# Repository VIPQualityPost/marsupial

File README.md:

# MARSUPIAL USB-PD + data hub
Marsupial (Motor And Regular Stuff USB PD Injector And Link) is a two port USB FS/HS hub which also is capable of injecting up to 60W per port (or 100W per port if I can implement USB PD EPR messages). The intended use for this is to be able to power and control motors over a single wire to both the motor and the PC, although it is fully USB PD compliant so you would be able to plug any other type of device into it. At the heart of the design is a programmable buck converter circuit which has a few predefined levels (5V, 9V, 12V, 15V, 20V, all at 3A, or 5A with EPR). In the future I would like to be able to implement Programmable Power Supply (PPS) functionality but at the moment this is out of scope of the project. It requires a large external 24V 120W power supply in order to power each port, and also features a daisy-chain connector on the back so that if you have multiple boards and a more powerful supply, you do not need to wire them all separately. The USB lines are brought out separately on an FFC connector so that the hub may be omitted and the signals manually handled off-board if desired.

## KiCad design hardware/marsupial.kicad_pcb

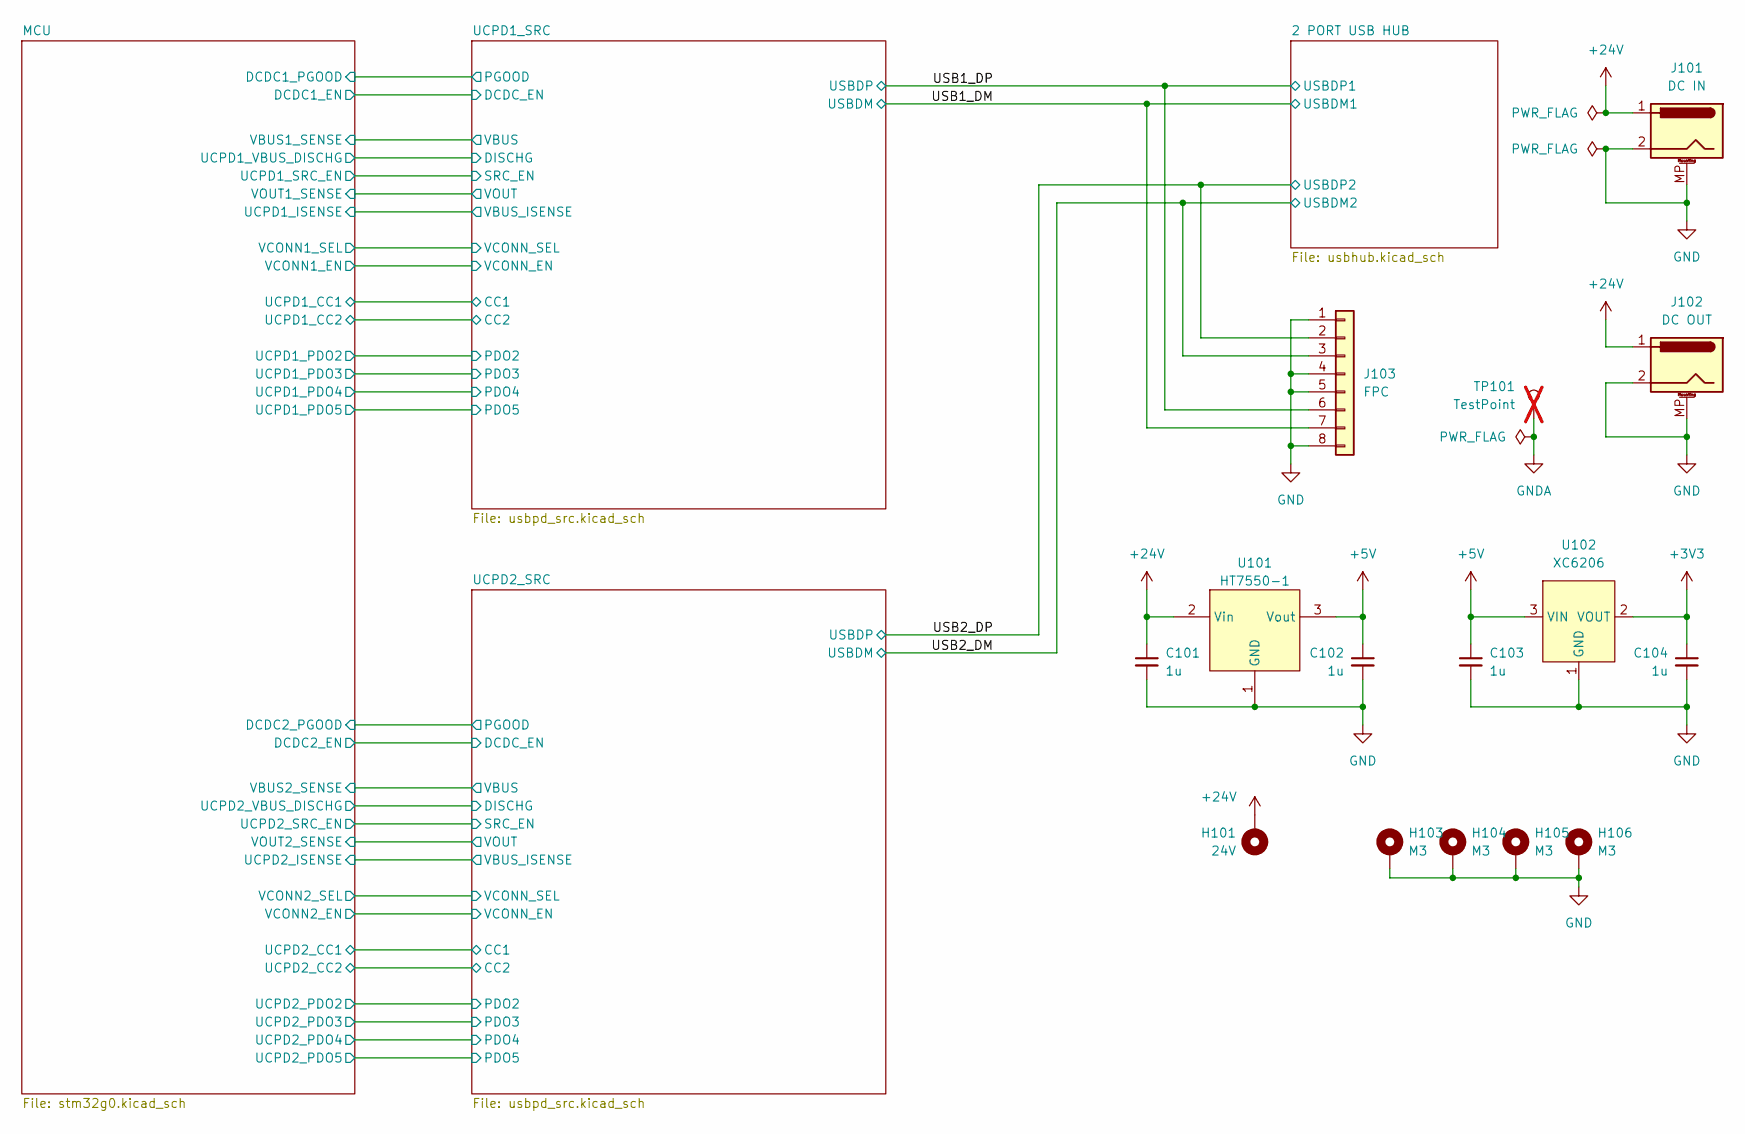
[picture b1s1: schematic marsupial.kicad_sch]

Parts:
C101, C102, C103, C104: 1u; C_0603_1608Metric; LCSC ID C15849
H101: 24V; MountingHole_3.2mm_M3_DIN965_Pad
H103, H104, H105, H106: M3; MountingHole_3.2mm_M3_DIN965_Pad
J101: DC IN; CONN-TH_XT30PW-M; LCSC ID C431092
J102: DC OUT; CONN-TH_XT30PW-M; LCSC ID C431092
J103: FPC; FPC-SMD_8P-P0.50_FPC-05F-8PH20; LCSC ID C2856797
TP101: TestPoint; not fitted
U101: HT7550-1; SOT-89-3; LCSC ID C16106
U102: XC6206; SOT-23; LCSC ID C5446

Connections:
+3V3: C104.1, U102.2 (VOUT); also elsewhere on the board
+5V: C102.1, C103.1, U101.3 (Vout), U102.3 (VIN); also elsewhere on the board
+24V: C101.1, H101.1, J101.1, J102.1, U101.2 (Vin); also elsewhere on the board
/USB1_DM: J103.7; also elsewhere on the board
/USB1_DP: J103.6; also elsewhere on the board
/USB2_DM: J103.3; also elsewhere on the board
/USB2_DP: J103.2; also elsewhere on the board
GND: C101.2, C102.2, C103.2, C104.2, H103.1, H104.1, H105.1, H106.1, J101.2, J101.MP (MountPin), J102.2, J102.MP (MountPin), J103.1, J103.4, J103.5, J103.8, U101.1 (GND), U102.1 (GND); also elsewhere on the board

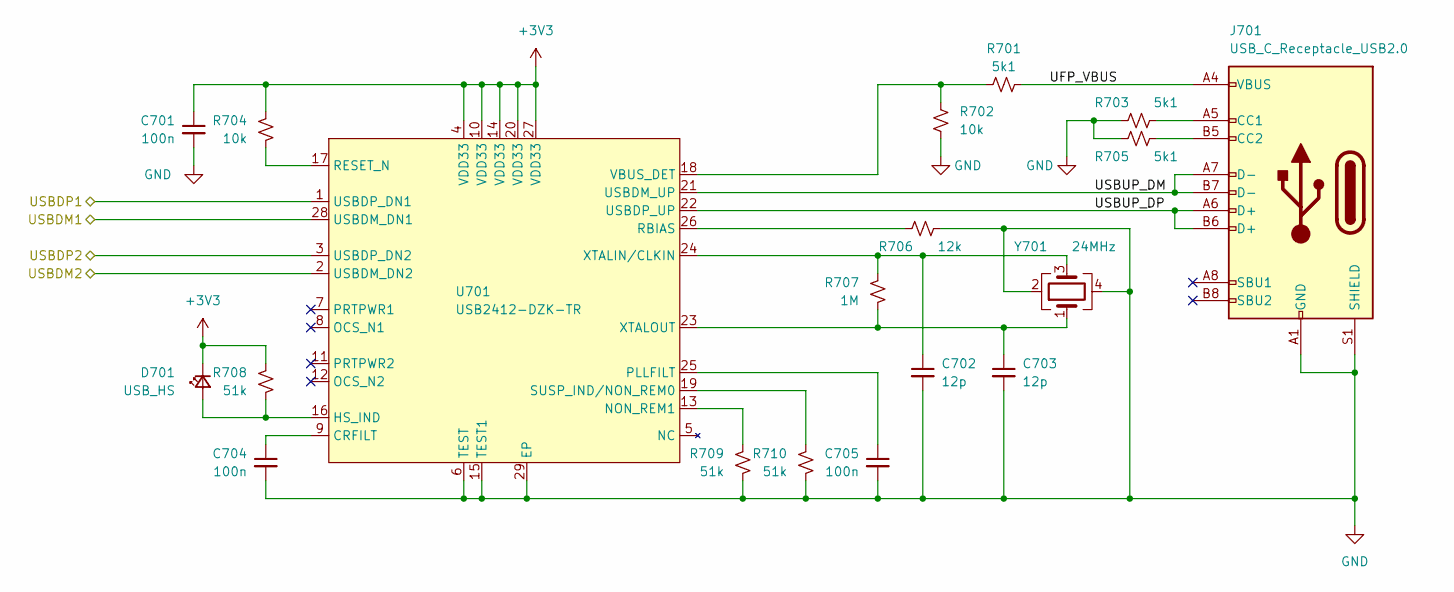
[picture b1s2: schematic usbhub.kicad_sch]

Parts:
C701: 100n; C_0402_1005Metric; LCSC ID C307331
C702, C703: 12p; C_0402_1005Metric; LCSC ID C1547
C704, C705: 100n; C_0603_1608Metric; LCSC ID C14663
D701: USB_HS; D_0603_1608Metric; LCSC ID C2290
J701: USB_C_Receptacle_USB2.0; HRO-TYPE-C-31-M-12; LCSC ID C165948
R701, R703, R705: 5k1; R_0402_1005Metric; LCSC ID C25905
R702, R704: 10k; R_0402_1005Metric; LCSC ID C25744
R706: 12k; R_0402_1005Metric; LCSC ID C25752
R707: 1M; R_0402_1005Metric; LCSC ID C26083
R708, R709, R710: 51k; R_0402_1005Metric; LCSC ID C25794
U701: USB2412-DZK-TR; QFN-28_L5.0-W5.0-P0.50-BL-EP3.3; LCSC ID C622609
Y701: 24MHz; Crystal_SMD_3225-4Pin_3.2x2.5mm; LCSC ID C70590

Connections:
+3V3: C701.1, D701.1 (K), R704.1, R708.1, U701.4 (VDD33), U701.10 (VDD33), U701.14 (VDD33), U701.20 (VDD33), U701.27 (VDD33); also elsewhere on the board
/2 PORT USB HUB/UFP_VBUS: J701.A4 (VBUS), J701.A9 (VBUS), J701.B4 (VBUS), J701.B9 (VBUS), R701.2
/2 PORT USB HUB/USBUP_DM: J701.A7 (D-), J701.B7 (D-), U701.21 (USBDM_UP)
/2 PORT USB HUB/USBUP_DP: J701.A6 (D+), J701.B6 (D+), U701.22 (USBDP_UP)
/USB1_DM: U701.28 (USBDM_DN1); also elsewhere on the board
/USB1_DP: U701.1 (USBDP_DN1); also elsewhere on the board
/USB2_DM: U701.2 (USBDM_DN2); also elsewhere on the board
/USB2_DP: U701.3 (USBDP_DN2); also elsewhere on the board
GND: C701.2, C702.2, C703.2, C704.2, C705.2, J701.A1 (GND), J701.A12 (GND), J701.B1 (GND), J701.B12 (GND), J701.S1 (SHIELD), R702.2, R703.1, R705.2, R706.1, R709.2, R710.2, U701.6 (TEST), U701.15 (TEST1), U701.29 (EP), Y701.2, Y701.4; also elsewhere on the board
unnamed: D701.2 (A), R708.2, U701.16 (HS_IND)
unnamed: J701.A5 (CC1), R703.2
unnamed: J701.B5 (CC2), R705.1
unnamed: C704.1, U701.9 (CRFILT)
unnamed: R709.1, U701.13 (NON_REM1)
unnamed: C705.1, U701.25 (PLLFILT)
unnamed: R706.2, U701.26 (RBIAS)
unnamed: R704.2, U701.17 (RESET_N)
unnamed: R710.1, U701.19 (SUSP_IND/NON_REM0)
unnamed: R701.1, R702.1, U701.18 (VBUS_DET)
unnamed: C702.1, R707.1, U701.24 (XTALIN/CLKIN), Y701.3
unnamed: C703.1, R707.2, U701.23 (XTALOUT), Y701.1

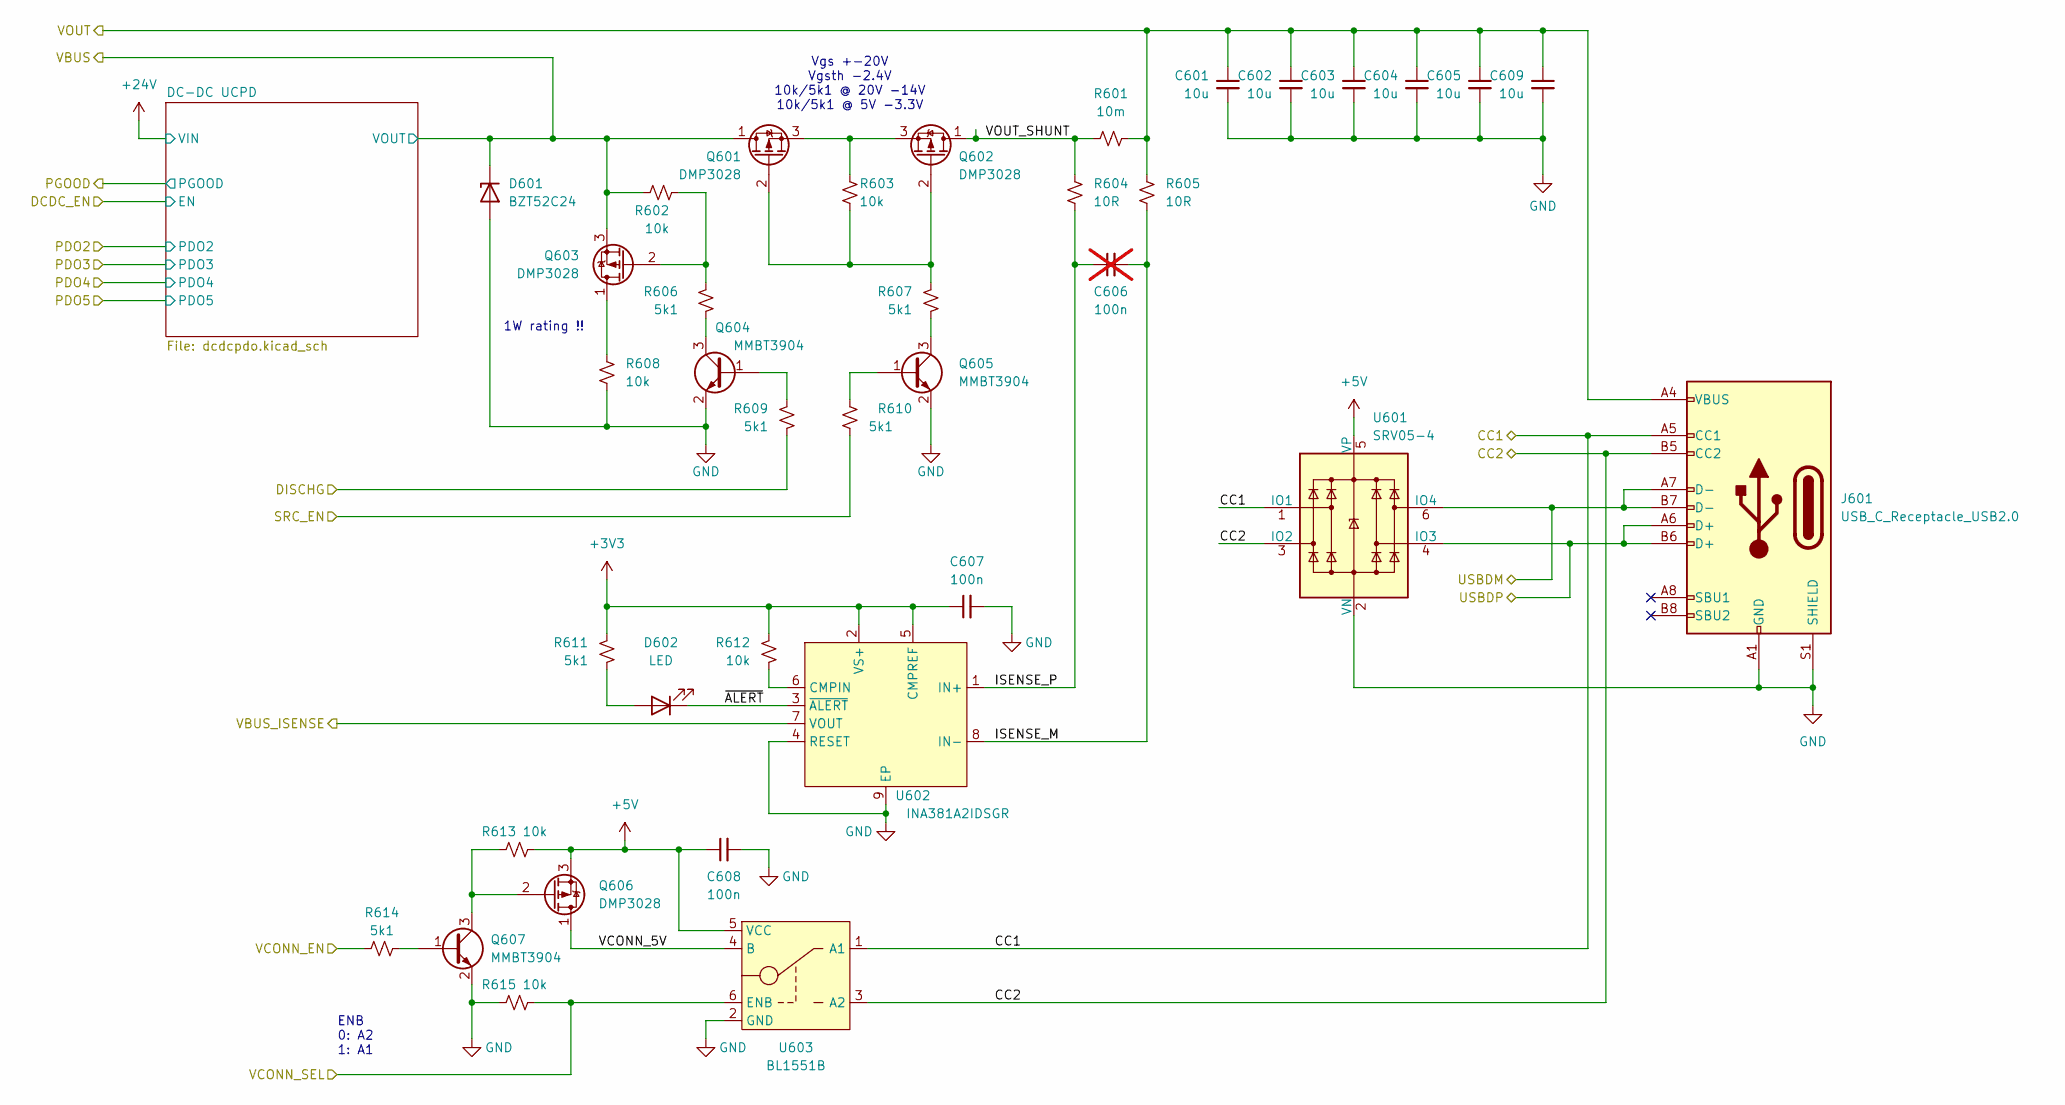
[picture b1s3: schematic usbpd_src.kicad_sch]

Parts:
C601, C602, C603, C604, C605, C609: 10u; C_0603_1608Metric; LCSC ID C96446
C606: 100n; C_0603_1608Metric; LCSC ID C14663; not fitted
C607, C608: 100n; C_0402_1005Metric; LCSC ID C307331
D601: BZT52C24; D_SOD-123; LCSC ID C727011
D602: LED; D_0603_1608Metric; LCSC ID C2290
J601: USB_C_Receptacle_USB2.0; HRO-TYPE-C-31-M-12; LCSC ID C165948
Q601, Q602, Q603, Q606: DMP3028; DMP3028-UDFN2020; LCSC ID C150441
Q604, Q605, Q607: MMBT3904; SOT-23; LCSC ID C20526
R601: 10m; R_1206_3216Metric; LCSC ID C2961483
R602, R603, R612, R613, R615: 10k; R_0402_1005Metric; LCSC ID C25744
R604, R605: 10R; R_0402_1005Metric; LCSC ID C25077
R606, R607, R609, R610, R611, R614: 5k1; R_0402_1005Metric; LCSC ID C25905
R608: 10k; R_0603_1608Metric; LCSC ID C25804
U601: SRV05-4; SOT-23-6; LCSC ID C7420376
U602: INA381A2IDSGR; WSON-8_L2.0-W2.0-P0.50-BL-EP0.9; LCSC ID C2155688
U603: BL1551B; SC-70-6_L2.1-W1.3-P0.65-LS2.3-BR; LCSC ID C2944066

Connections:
+3V3: C607.1, R611.1, R612.1, U602.2 (VS+), U602.5 (CMPREF); also elsewhere on the board
+5V: C608.1, Q606.3 (S), R613.2, U601.5 (VP), U603.5 (VCC); also elsewhere on the board
/MCU/UCPD1_ISENSE: U602.7 (VOUT); also elsewhere on the board
/MCU/UCPD1_SRC_EN: R610.2; also elsewhere on the board
/MCU/UCPD1_VBUS_DISCHG: R609.2; also elsewhere on the board
/MCU/VBUS1_SENSE: D601.1 (K), Q601.1 (D), Q603.3 (S), R602.1; also elsewhere on the board
/MCU/VCONN1_EN: R614.1; also elsewhere on the board
/MCU/VCONN1_SEL: R615.2, U603.6 (ENB); also elsewhere on the board
/MCU/VOUT1_SENSE: C601.1, C602.1, C603.1, C604.1, C605.1, C609.1, J601.A4 (VBUS), J601.A9 (VBUS), J601.B4 (VBUS), J601.B9 (VBUS), R601.2, R605.1; also elsewhere on the board
/UCPD1_SRC/CC1: J601.A5 (CC1), U601.1 (IO1), U603.1 (A1); also elsewhere on the board
/UCPD1_SRC/CC2: J601.B5 (CC2), U601.3 (IO2), U603.3 (A2); also elsewhere on the board
/UCPD1_SRC/ISENSE_M: C606.2, R605.2, U602.8 (IN-)
/UCPD1_SRC/ISENSE_P: C606.1, R604.2, U602.1 (IN+)
/UCPD1_SRC/VCONN_5V: Q606.1 (D), U603.4 (B)
/UCPD1_SRC/VOUT_SHUNT: Q602.1 (D), R601.1, R604.1
/UCPD1_SRC/~ALERT: D602.1 (K), U602.3 (~ALERT)
/USB1_DM: J601.A7 (D-), J601.B7 (D-), U601.6 (IO4); also elsewhere on the board
/USB1_DP: J601.A6 (D+), J601.B6 (D+), U601.4 (IO3); also elsewhere on the board
GND: C601.2, C602.2, C603.2, C604.2, C605.2, C607.2, C608.2, C609.2, D601.2 (A), J601.A1 (GND), J601.A12 (GND), J601.B1 (GND), J601.B12 (GND), J601.S1 (SHIELD), Q604.2 (E), Q605.2 (E), Q607.2 (E), R608.2, R615.1, U601.2 (VN), U602.4 (RESET), U602.9 (EP), U603.2 (GND); also elsewhere on the board
unnamed: D602.2 (A), R611.2
unnamed: Q601.2 (G), Q602.2 (G), R603.2, R607.1
unnamed: Q601.3 (S), Q602.3 (S), R603.1
unnamed: Q603.1 (D), R608.1
unnamed: Q603.2 (G), R602.2, R606.1
unnamed: Q604.1 (B), R609.1
unnamed: Q604.3 (C), R606.2
unnamed: Q605.1 (B), R610.1
unnamed: Q605.3 (C), R607.2
unnamed: Q606.2 (G), Q607.3 (C), R613.1
unnamed: Q607.1 (B), R614.2
unnamed: R612.2, U602.6 (CMPIN)

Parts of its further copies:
C201, C202, C203, C204, C205, C209: 10u; C_0603_1608Metric; LCSC ID C96446
C206: 100n; C_0603_1608Metric; LCSC ID C14663; not fitted
C207, C208: 100n; C_0402_1005Metric; LCSC ID C307331
D201: BZT52C24; D_SOD-123; LCSC ID C727011
D202: LED; D_0603_1608Metric; LCSC ID C2290
J201: USB_C_Receptacle_USB2.0; HRO-TYPE-C-31-M-12; LCSC ID C165948
Q201, Q202, Q203, Q206: DMP3028; DMP3028-UDFN2020; LCSC ID C150441
Q204, Q205, Q207: MMBT3904; SOT-23; LCSC ID C20526
R201: 10m; R_1206_3216Metric; LCSC ID C2961483
R202, R203, R212, R213, R215: 10k; R_0402_1005Metric; LCSC ID C25744
R204, R205: 10R; R_0402_1005Metric; LCSC ID C25077
R206, R207, R209, R210, R211, R214: 5k1; R_0402_1005Metric; LCSC ID C25905
R208: 10k; R_0603_1608Metric; LCSC ID C25804
U201: SRV05-4; SOT-23-6; LCSC ID C7420376
U202: INA381A2IDSGR; WSON-8_L2.0-W2.0-P0.50-BL-EP0.9; LCSC ID C2155688
U203: BL1551B; SC-70-6_L2.1-W1.3-P0.65-LS2.3-BR; LCSC ID C2944066

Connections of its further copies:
+3V3: C207.1, R211.1, R212.1, U202.2 (VS+), U202.5 (CMPREF); also elsewhere on the board
+5V: C208.1, Q206.3 (S), R213.2, U201.5 (VP), U203.5 (VCC); also elsewhere on the board
/MCU/UCPD2_ISENSE: U202.7 (VOUT); also elsewhere on the board
/MCU/UCPD2_SRC_EN: R210.2; also elsewhere on the board
/MCU/UCPD2_VBUS_DISCHG: R209.2; also elsewhere on the board
/MCU/VBUS2_SENSE: D201.1 (K), Q201.1 (D), Q203.3 (S), R202.1; also elsewhere on the board
/MCU/VCONN2_EN: R214.1; also elsewhere on the board
/MCU/VCONN2_SEL: R215.2, U203.6 (ENB); also elsewhere on the board
/MCU/VOUT2_SENSE: C201.1, C202.1, C203.1, C204.1, C205.1, C209.1, J201.A4 (VBUS), J201.A9 (VBUS), J201.B4 (VBUS), J201.B9 (VBUS), R201.2, R205.1; also elsewhere on the board
/UCPD2_SRC/CC1: J201.A5 (CC1), U201.1 (IO1), U203.1 (A1); also elsewhere on the board
/UCPD2_SRC/CC2: J201.B5 (CC2), U201.3 (IO2), U203.3 (A2); also elsewhere on the board
/UCPD2_SRC/ISENSE_M: C206.2, R205.2, U202.8 (IN-)
/UCPD2_SRC/ISENSE_P: C206.1, R204.2, U202.1 (IN+)
/UCPD2_SRC/VCONN_5V: Q206.1 (D), U203.4 (B)
/UCPD2_SRC/VOUT_SHUNT: Q202.1 (D), R201.1, R204.1
/UCPD2_SRC/~ALERT: D202.1 (K), U202.3 (~ALERT)
/USB2_DM: J201.A7 (D-), J201.B7 (D-), U201.6 (IO4); also elsewhere on the board
/USB2_DP: J201.A6 (D+), J201.B6 (D+), U201.4 (IO3); also elsewhere on the board
GND: C201.2, C202.2, C203.2, C204.2, C205.2, C207.2, C208.2, C209.2, D201.2 (A), J201.A1 (GND), J201.A12 (GND), J201.B1 (GND), J201.B12 (GND), J201.S1 (SHIELD), Q204.2 (E), Q205.2 (E), Q207.2 (E), R208.2, R215.1, U201.2 (VN), U202.4 (RESET), U202.9 (EP), U203.2 (GND); also elsewhere on the board
unnamed: D202.2 (A), R211.2
unnamed: Q201.2 (G), Q202.2 (G), R203.2, R207.1
unnamed: Q201.3 (S), Q202.3 (S), R203.1
unnamed: Q203.1 (D), R208.1
unnamed: Q203.2 (G), R202.2, R206.1
unnamed: Q204.1 (B), R209.1
unnamed: Q204.3 (C), R206.2
unnamed: Q205.1 (B), R210.1
unnamed: Q205.3 (C), R207.2
unnamed: Q206.2 (G), Q207.3 (C), R213.1
unnamed: Q207.1 (B), R214.2
unnamed: R212.2, U202.6 (CMPIN)

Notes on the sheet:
Vgs +-20V Vgsth -2.4V 10k/5k1 @ 20V -14V 10k/5k1 @ 5V -3.3V
ENB 0: A2 1: A1
1W rating !!

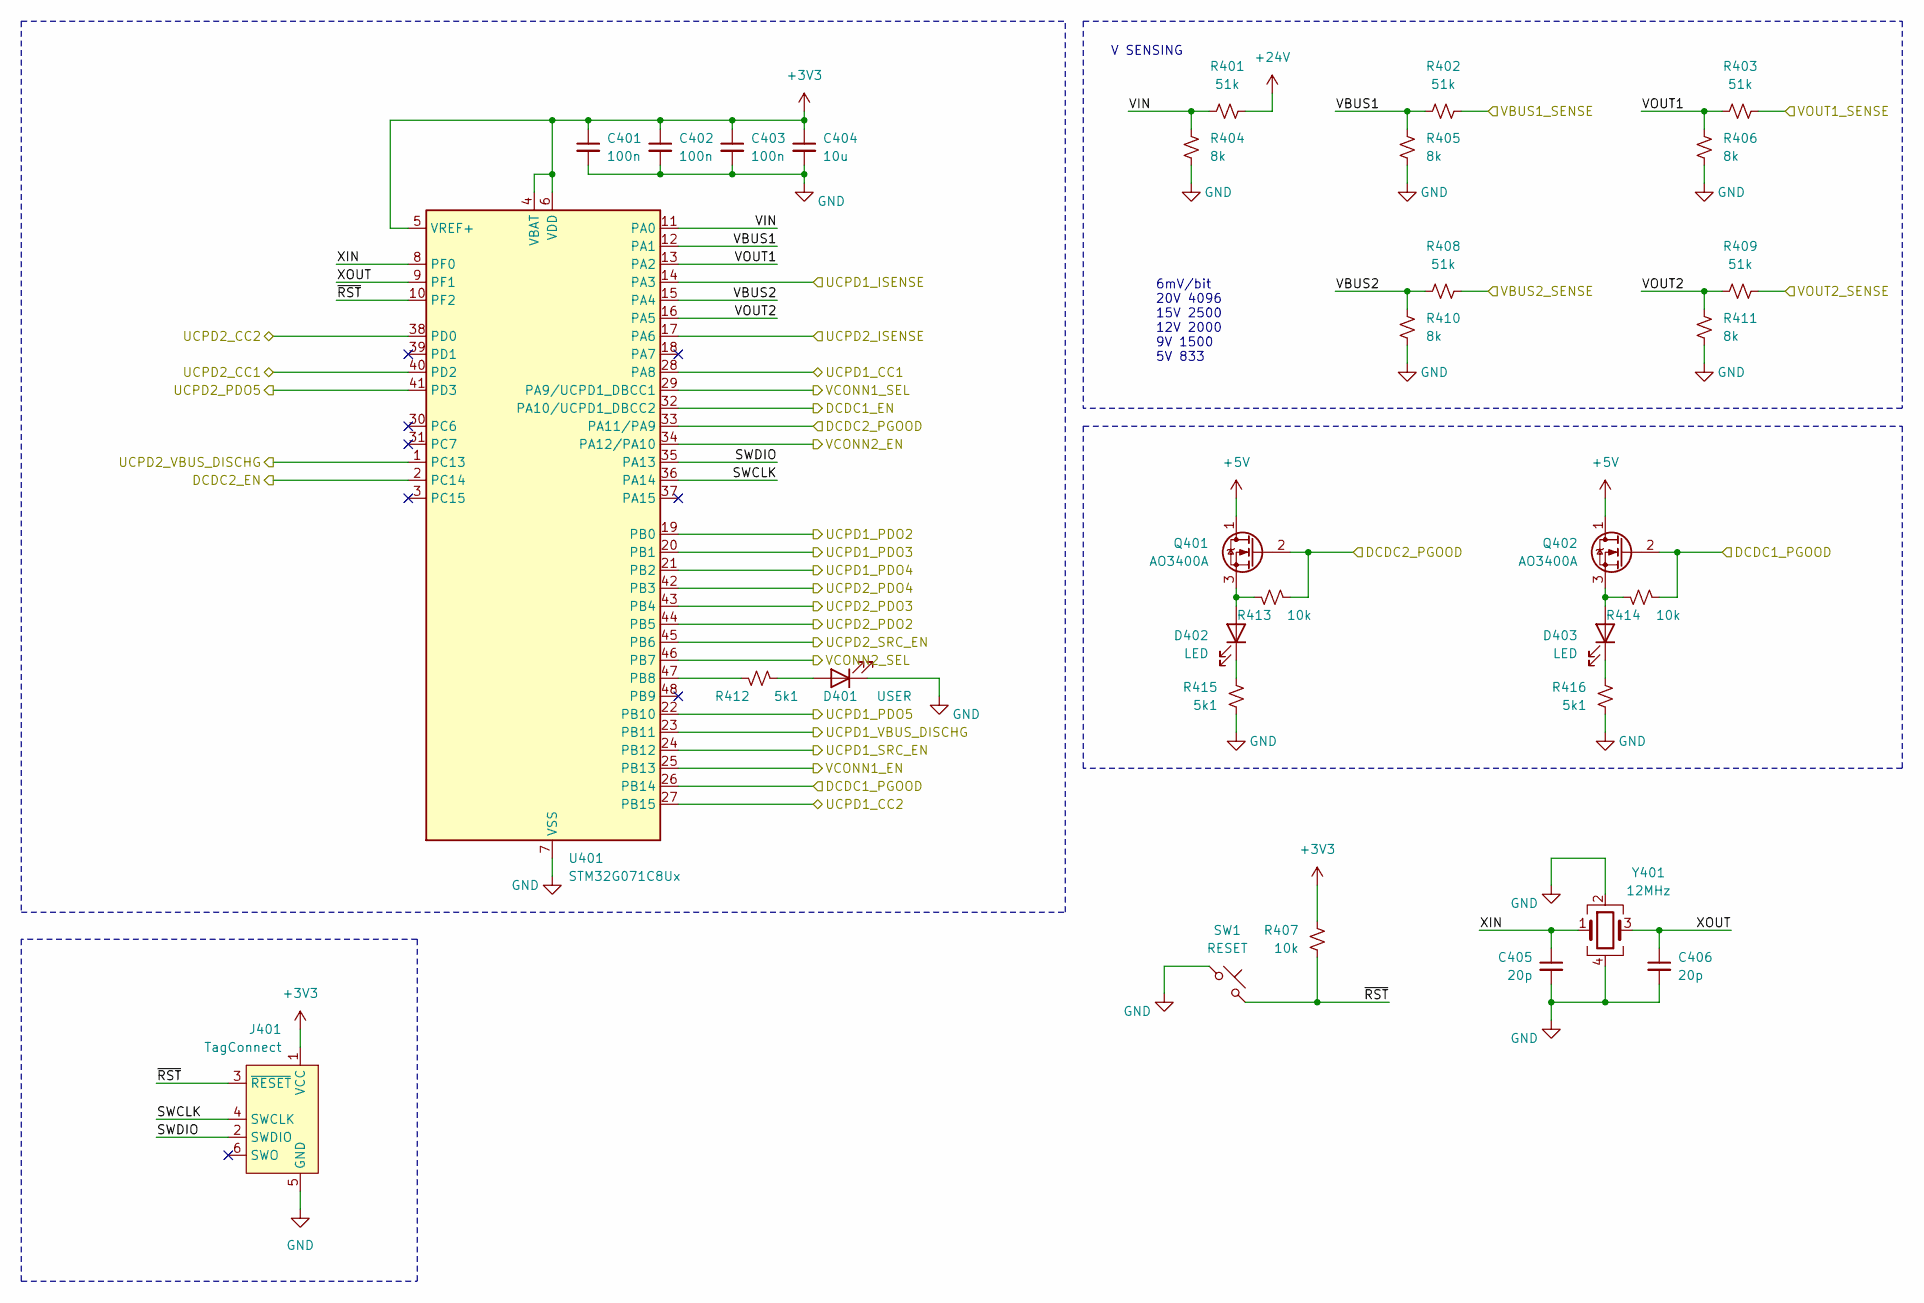
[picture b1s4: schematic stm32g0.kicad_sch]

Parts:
C401, C402, C403: 100n; C_0402_1005Metric; LCSC ID C307331
C404: 10u; C_0603_1608Metric; LCSC ID C96446
C405, C406: 20p; C_0402_1005Metric; LCSC ID C1554
D401: USER; D_0603_1608Metric; LCSC ID C2290
D402, D403: LED; D_0603_1608Metric; LCSC ID C2290
J401: TagConnect; Tag-Connect_TC2030-IDC-NL_2x03_P1.27mm_Vertical
Q401, Q402: AO3400A; TSOT-23; LCSC ID AO3400A
R401, R402, R403, R408, R409: 51k; R_0402_1005Metric; LCSC ID C25794
R404, R405, R406, R410, R411: 8k; R_0402_1005Metric; LCSC ID C137947
R407, R413, R414: 10k; R_0402_1005Metric; LCSC ID C25744
R412, R415, R416: 5k1; R_0402_1005Metric; LCSC ID C25905
SW1: RESET; TS-1187A-B-A-B; LCSC ID C318884
U401: STM32G071C8Ux; QFN-48-1EP_7x7mm_P0.5mm_EP5.6x5.6mm; LCSC ID C3014317
Y401: 12MHz; Crystal_SMD_3225-4Pin_3.2x2.5mm; LCSC ID C9002

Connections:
+3V3: C401.1, C402.1, C403.1, C404.1, J401.1 (VCC), R407.1, U401.4 (VBAT), U401.5 (VREF+), U401.6 (VDD); also elsewhere on the board
+5V: Q401.1 (D), Q402.1 (D); also elsewhere on the board
+24V: R401.2; also elsewhere on the board
/MCU/DCDC1_EN: U401.32 (PA10/UCPD1_DBCC2); also elsewhere on the board
/MCU/DCDC1_PGOOD: Q402.2 (G), R414.2, U401.26 (PB14); also elsewhere on the board
/MCU/DCDC2_EN: U401.2 (PC14); also elsewhere on the board
/MCU/DCDC2_PGOOD: Q401.2 (G), R413.2, U401.33 (PA11/PA9); also elsewhere on the board
/MCU/SWCLK: J401.4 (SWCLK), U401.36 (PA14)
/MCU/SWDIO: J401.2 (SWDIO), U401.35 (PA13)
/MCU/UCPD1_ISENSE: U401.14 (PA3); also elsewhere on the board
/MCU/UCPD1_PDO2: U401.19 (PB0); also elsewhere on the board
/MCU/UCPD1_PDO3: U401.20 (PB1); also elsewhere on the board
/MCU/UCPD1_PDO4: U401.21 (PB2); also elsewhere on the board
/MCU/UCPD1_PDO5: U401.22 (PB10); also elsewhere on the board
/MCU/UCPD1_SRC_EN: U401.24 (PB12); also elsewhere on the board
/MCU/UCPD1_VBUS_DISCHG: U401.23 (PB11); also elsewhere on the board
/MCU/UCPD2_ISENSE: U401.17 (PA6); also elsewhere on the board
/MCU/UCPD2_PDO2: U401.44 (PB5); also elsewhere on the board
/MCU/UCPD2_PDO3: U401.43 (PB4); also elsewhere on the board
/MCU/UCPD2_PDO4: U401.42 (PB3); also elsewhere on the board
/MCU/UCPD2_PDO5: U401.41 (PD3); also elsewhere on the board
/MCU/UCPD2_SRC_EN: U401.45 (PB6); also elsewhere on the board
/MCU/UCPD2_VBUS_DISCHG: U401.1 (PC13); also elsewhere on the board
/MCU/VBUS1: R402.1, R405.1, U401.12 (PA1)
/MCU/VBUS1_SENSE: R402.2; also elsewhere on the board
/MCU/VBUS2: R408.1, R410.1, U401.15 (PA4)
/MCU/VBUS2_SENSE: R408.2; also elsewhere on the board
/MCU/VCONN1_EN: U401.25 (PB13); also elsewhere on the board
/MCU/VCONN1_SEL: U401.29 (PA9/UCPD1_DBCC1); also elsewhere on the board
/MCU/VCONN2_EN: U401.34 (PA12/PA10); also elsewhere on the board
/MCU/VCONN2_SEL: U401.46 (PB7); also elsewhere on the board
/MCU/VIN: R401.1, R404.1, U401.11 (PA0)
/MCU/VOUT1: R403.1, R406.1, U401.13 (PA2)
/MCU/VOUT1_SENSE: R403.2; also elsewhere on the board
/MCU/VOUT2: R409.1, R411.1, U401.16 (PA5)
/MCU/VOUT2_SENSE: R409.2; also elsewhere on the board
/MCU/XIN: C405.1, U401.8 (PF0), Y401.1
/MCU/XOUT: C406.1, U401.9 (PF1), Y401.3
/MCU/~RST: J401.3 (~RESET), R407.2, SW1.2, U401.10 (PF2)
/UCPD1_SRC/CC1: U401.28 (PA8); also elsewhere on the board
/UCPD1_SRC/CC2: U401.27 (PB15); also elsewhere on the board
/UCPD2_SRC/CC1: U401.40 (PD2); also elsewhere on the board
/UCPD2_SRC/CC2: U401.38 (PD0); also elsewhere on the board
GND: C401.2, C402.2, C403.2, C404.2, C405.2, C406.2, D401.1 (K), J401.5 (GND), R404.2, R405.2, R406.2, R410.2, R411.2, R415.2, R416.2, SW1.1, U401.7 (VSS), U401.49 (VSS), Y401.2, Y401.4; also elsewhere on the board
unnamed: D401.2 (A), R412.2
unnamed: D402.2 (A), Q401.3 (S), R413.1
unnamed: D402.1 (K), R415.1
unnamed: D403.2 (A), Q402.3 (S), R414.1
unnamed: D403.1 (K), R416.1
unnamed: R412.1, U401.47 (PB8)

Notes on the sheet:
V SENSING
6mV/bit 20V 4096 15V 2500 12V 2000 9V 1500 5V 833

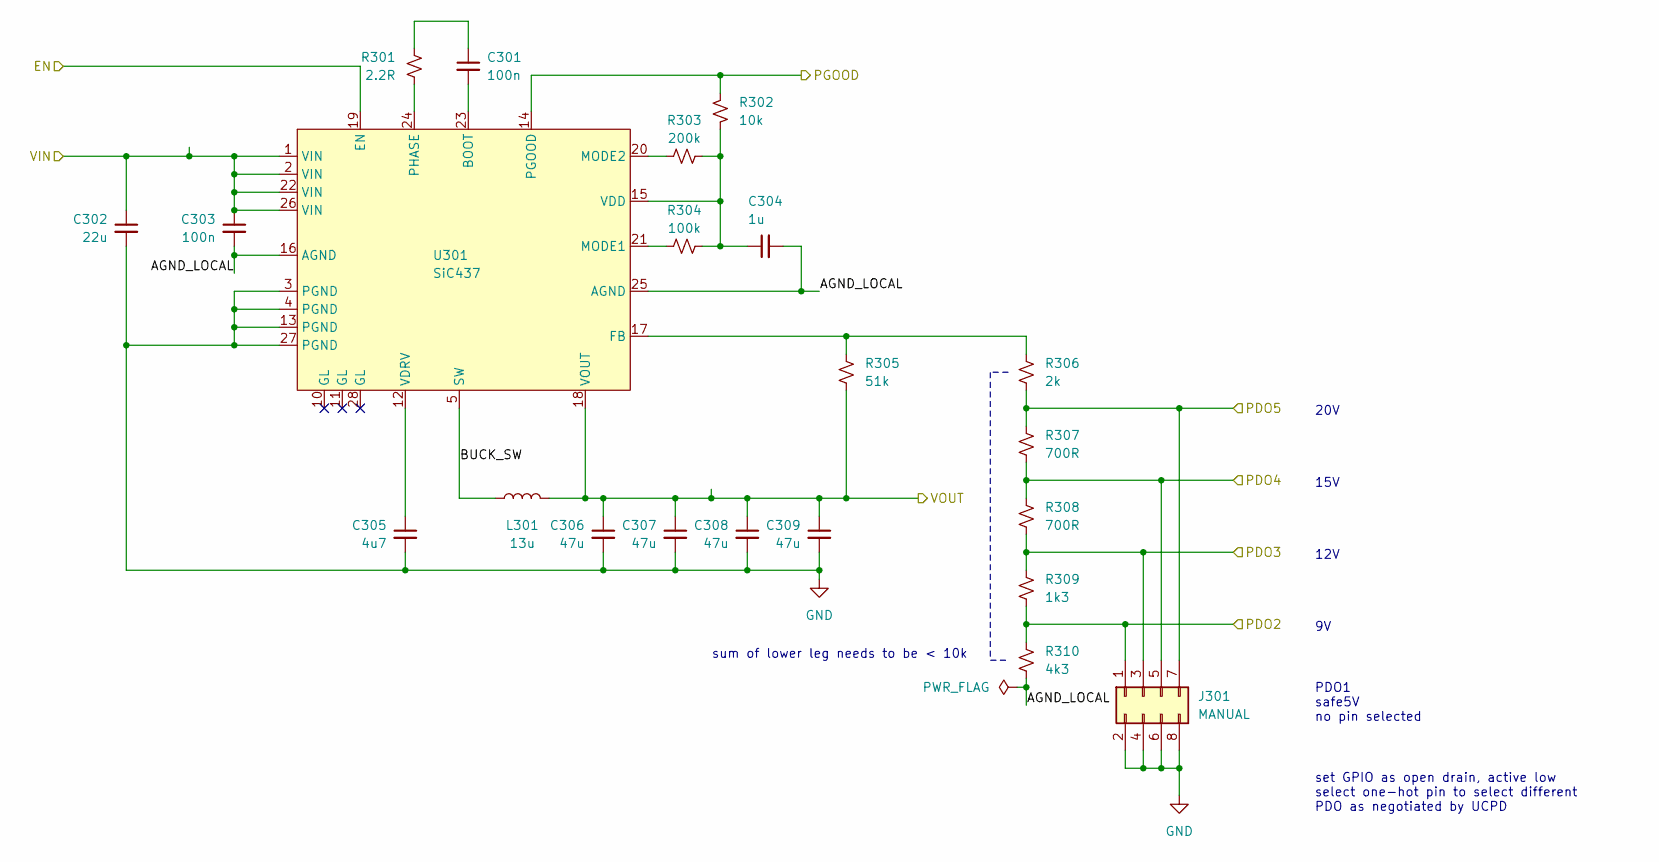
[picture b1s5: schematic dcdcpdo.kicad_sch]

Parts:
C301, C303: 100n; C_0603_1608Metric; LCSC ID C14663
C302: 22u; C_0805_2012Metric; LCSC ID C45783
C304: 1u; C_0603_1608Metric; LCSC ID C15849
C305: 4u7; C_0603_1608Metric; LCSC ID C19666
C306, C307, C308, C309: 47u; C_1206_3216Metric; LCSC ID C76659
J301: MANUAL; PinHeader_2x04_P1.27mm_Vertical; LCSC ID C2685182
L301: 13u; IND-SMD_L5.2-W5.4; LCSC ID C524588
R301: 2.2R; R_0603_1608Metric; LCSC ID C22939
R302: 10k; R_0402_1005Metric; LCSC ID C25744
R303: 200k; R_0402_1005Metric; LCSC ID C25764
R304: 100k; R_0402_1005Metric; LCSC ID C25741
R305: 51k; R_0402_1005Metric; LCSC ID C25794
R306: 2k; R_0402_1005Metric; LCSC ID C4109
R307, R308: 700R; R_0402_1005Metric; LCSC ID C728428
R309: 1k3; R_0402_1005Metric; LCSC ID C25866
R310: 4k3; R_0402_1005Metric; LCSC ID C25899
U301: SiC437; SiC437AED; LCSC ID C2071432

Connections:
+24V: C302.1, C303.1, U301.1 (VIN), U301.2 (VIN), U301.22 (VIN), U301.26 (VIN); also elsewhere on the board
/MCU/DCDC1_EN: U301.19 (EN); also elsewhere on the board
/MCU/DCDC1_PGOOD: R302.1, U301.14 (PGOOD); also elsewhere on the board
/MCU/UCPD1_PDO2: J301.1, R309.2, R310.1; also elsewhere on the board
/MCU/UCPD1_PDO3: J301.3, R308.2, R309.1; also elsewhere on the board
/MCU/UCPD1_PDO4: J301.5, R307.2, R308.1; also elsewhere on the board
/MCU/UCPD1_PDO5: J301.7, R306.2, R307.1; also elsewhere on the board
/MCU/VBUS1_SENSE: C306.1, C307.1, C308.1, C309.1, L301.2, R305.2, U301.18 (VOUT); also elsewhere on the board
/UCPD1_SRC/DC-DC UCPD/AGND_LOCAL: C303.2, C304.2, R310.2, U301.16 (AGND), U301.25 (AGND)
/UCPD1_SRC/DC-DC UCPD/BUCK_SW: L301.1, U301.5 (SW), U301.6 (SW), U301.7 (SW), U301.8 (SW), U301.9 (SW)
GND: C302.2, C305.2, C306.2, C307.2, C308.2, C309.2, J301.2, J301.4, J301.6, J301.8, U301.3 (PGND), U301.4 (PGND), U301.13 (PGND), U301.27 (PGND); also elsewhere on the board
unnamed: C301.1, R301.1
unnamed: C301.2, U301.23 (BOOT)
unnamed: R305.1, R306.1, U301.17 (FB)
unnamed: R304.1, U301.21 (MODE1)
unnamed: R303.1, U301.20 (MODE2)
unnamed: R301.2, U301.24 (PHASE)
unnamed: C304.1, R302.2, R303.2, R304.2, U301.15 (VDD)
unnamed: C305.1, U301.12 (VDRV)

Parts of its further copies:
C501, C503: 100n; C_0603_1608Metric; LCSC ID C14663
C502: 22u; C_0805_2012Metric; LCSC ID C45783
C504: 1u; C_0603_1608Metric; LCSC ID C15849
C505: 4u7; C_0603_1608Metric; LCSC ID C19666
C506, C507, C508, C509: 47u; C_1206_3216Metric; LCSC ID C76659
J501: MANUAL; PinHeader_2x04_P1.27mm_Vertical; LCSC ID C2685182
L501: 13u; IND-SMD_L5.2-W5.4; LCSC ID C524588
R501: 2.2R; R_0603_1608Metric; LCSC ID C22939
R502: 10k; R_0402_1005Metric; LCSC ID C25744
R503: 200k; R_0402_1005Metric; LCSC ID C25764
R504: 100k; R_0402_1005Metric; LCSC ID C25741
R505: 51k; R_0402_1005Metric; LCSC ID C25794
R506: 2k; R_0402_1005Metric; LCSC ID C4109
R507, R508: 700R; R_0402_1005Metric; LCSC ID C728428
R509: 1k3; R_0402_1005Metric; LCSC ID C25866
R510: 4k3; R_0402_1005Metric; LCSC ID C25899
U501: SiC437; SiC437AED; LCSC ID C2071432

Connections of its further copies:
+24V: C502.1, C503.1, U501.1 (VIN), U501.2 (VIN), U501.22 (VIN), U501.26 (VIN); also elsewhere on the board
/MCU/DCDC2_EN: U501.19 (EN); also elsewhere on the board
/MCU/DCDC2_PGOOD: R502.1, U501.14 (PGOOD); also elsewhere on the board
/MCU/UCPD2_PDO2: J501.1, R509.2, R510.1; also elsewhere on the board
/MCU/UCPD2_PDO3: J501.3, R508.2, R509.1; also elsewhere on the board
/MCU/UCPD2_PDO4: J501.5, R507.2, R508.1; also elsewhere on the board
/MCU/UCPD2_PDO5: J501.7, R506.2, R507.1; also elsewhere on the board
/MCU/VBUS2_SENSE: C506.1, C507.1, C508.1, C509.1, L501.2, R505.2, U501.18 (VOUT); also elsewhere on the board
/UCPD2_SRC/DC-DC UCPD/AGND_LOCAL: C503.2, C504.2, R510.2, U501.16 (AGND), U501.25 (AGND)
/UCPD2_SRC/DC-DC UCPD/BUCK_SW: L501.1, U501.5 (SW), U501.6 (SW), U501.7 (SW), U501.8 (SW), U501.9 (SW)
GND: C502.2, C505.2, C506.2, C507.2, C508.2, C509.2, J501.2, J501.4, J501.6, J501.8, U501.3 (PGND), U501.4 (PGND), U501.13 (PGND), U501.27 (PGND); also elsewhere on the board
unnamed: C501.1, R501.1
unnamed: C501.2, U501.23 (BOOT)
unnamed: R505.1, R506.1, U501.17 (FB)
unnamed: R504.1, U501.21 (MODE1)
unnamed: R503.1, U501.20 (MODE2)
unnamed: R501.2, U501.24 (PHASE)
unnamed: C504.1, R502.2, R503.2, R504.2, U501.15 (VDD)
unnamed: C505.1, U501.12 (VDRV)

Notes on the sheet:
sum of lower leg needs to be < 10k
20V
set GPIO as open drain, active low select one-hot pin to select different PDO as negotiated by UCPD
PDO1 safe5V no pin selected
12V
15V

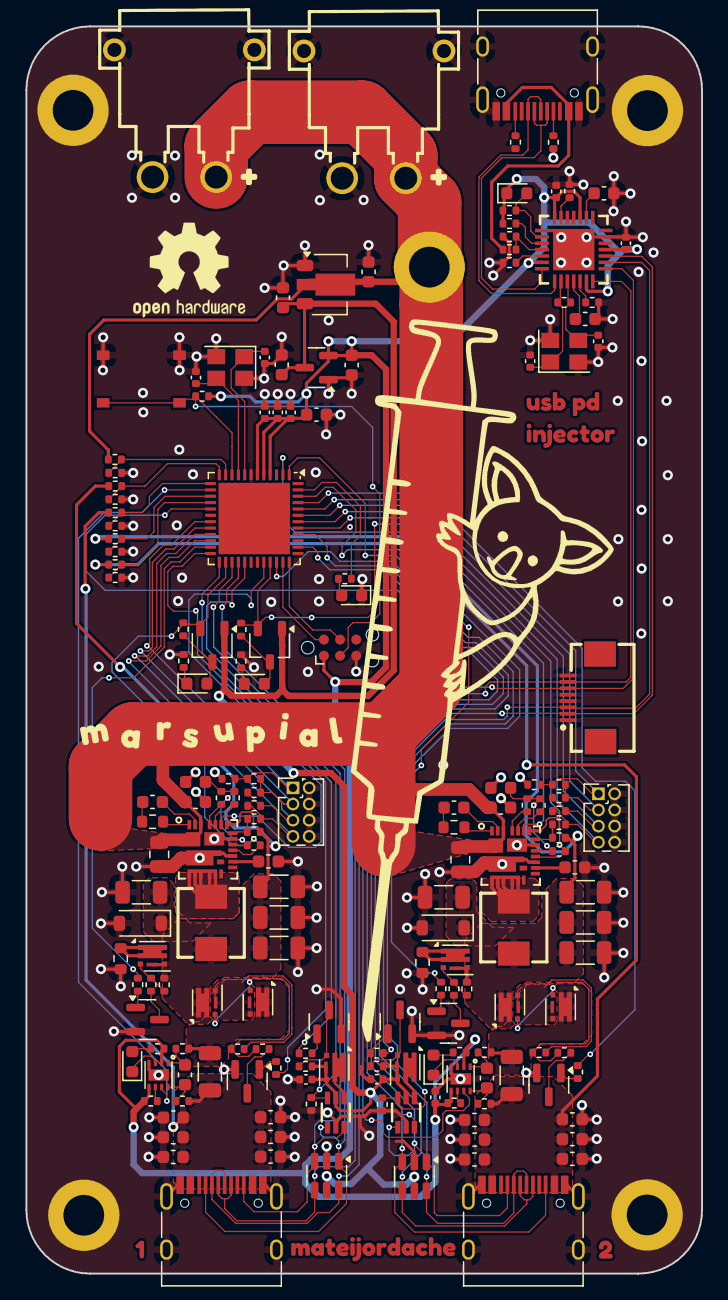
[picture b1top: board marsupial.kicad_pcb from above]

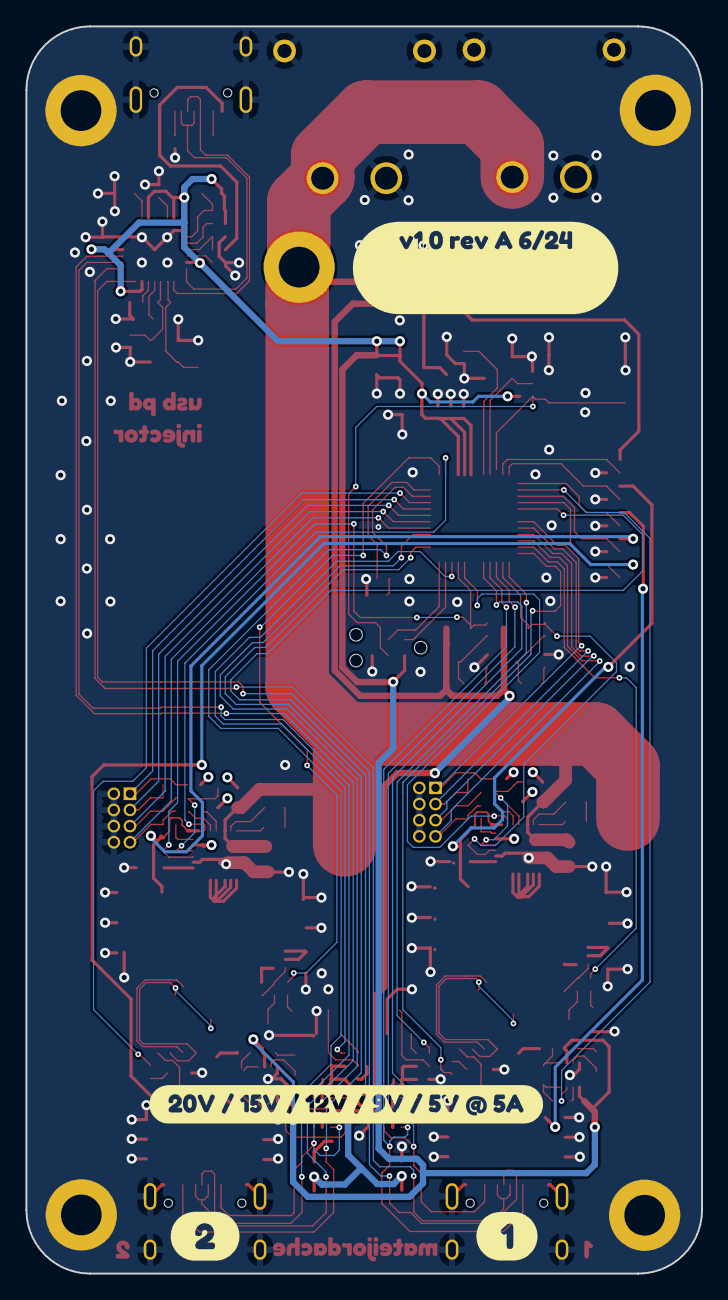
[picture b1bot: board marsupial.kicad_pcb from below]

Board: 4 copper layers, 53.1 x 98.0 mm, 204 parts (6 on the bottom side), 123 nets.

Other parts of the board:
PCB1: PCB; bud_9162
kibuzzard-6664A222, kibuzzard-6664A222#2: G***; kibuzzard-6664A222
kibuzzard-6664BF3A: G***; kibuzzard-6664BF3A
kibuzzard-6664CCCB: G***; kibuzzard-6664CCCB
kibuzzard-6664CCD3: G***; kibuzzard-6664CCD3
kibuzzard-6664CE0F: G***; kibuzzard-6664CE0F
kibuzzard-6664CE29: G***; kibuzzard-6664CE29
kibuzzard-6664CEA1: G***; kibuzzard-6664CEA1
kibuzzard-6664CEA9: G***; kibuzzard-6664CEA9
kibuzzard-6664CEEC: G***; kibuzzard-6664CEEC
kibuzzard-6664CF7E: G***; kibuzzard-6664CF7E
kibuzzard-6664D6A2: G***; kibuzzard-6664D6A2
kibuzzard-6664D6A7: G***; kibuzzard-6664D6A7
kibuzzard-6664D67C: G***; kibuzzard-6664D67C
kibuzzard-6664D69E: G***; kibuzzard-6664D69E
kibuzzard-6664D661: G***; kibuzzard-6664D661
kibuzzard-6664D670: G***; kibuzzard-6664D670
kibuzzard-6664D680: G***; kibuzzard-6664D680
kibuzzard-6664D691: G***; kibuzzard-6664D691
kibuzzard-6664D696: G***; kibuzzard-6664D696
kibuzzard-66649A48: G***; kibuzzard-66649A48

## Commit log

2024-06-12 initial release
2024-06-12 add board art
2024-06-12 add platformio config
2024-06-12 add cubemx code
2024-06-12 switch to makefile
2024-06-12 add CI workflow
2024-06-12 add image and readme
2024-06-12 readme typo
2024-06-12 fix typos in readme
2024-06-12 Add design file PDFs to repo [skip ci]
2024-06-12 finish artwork
2024-06-12 Update board art
2024-06-12 clean up drc
2024-06-12 fix image
2024-06-12 drc errors?
2024-06-12 oh my god fix the image
2024-06-13 try to fix edge cuts
2024-06-13 Fix SiC437 footprint and LCSC field error
2024-06-13 clean drc
2024-06-13 fix silkscreen
2024-06-23 add enclosure coverplates
2024-08-18 change to C8U3 variant
2024-10-04 fix pinout issues hw rev 1
